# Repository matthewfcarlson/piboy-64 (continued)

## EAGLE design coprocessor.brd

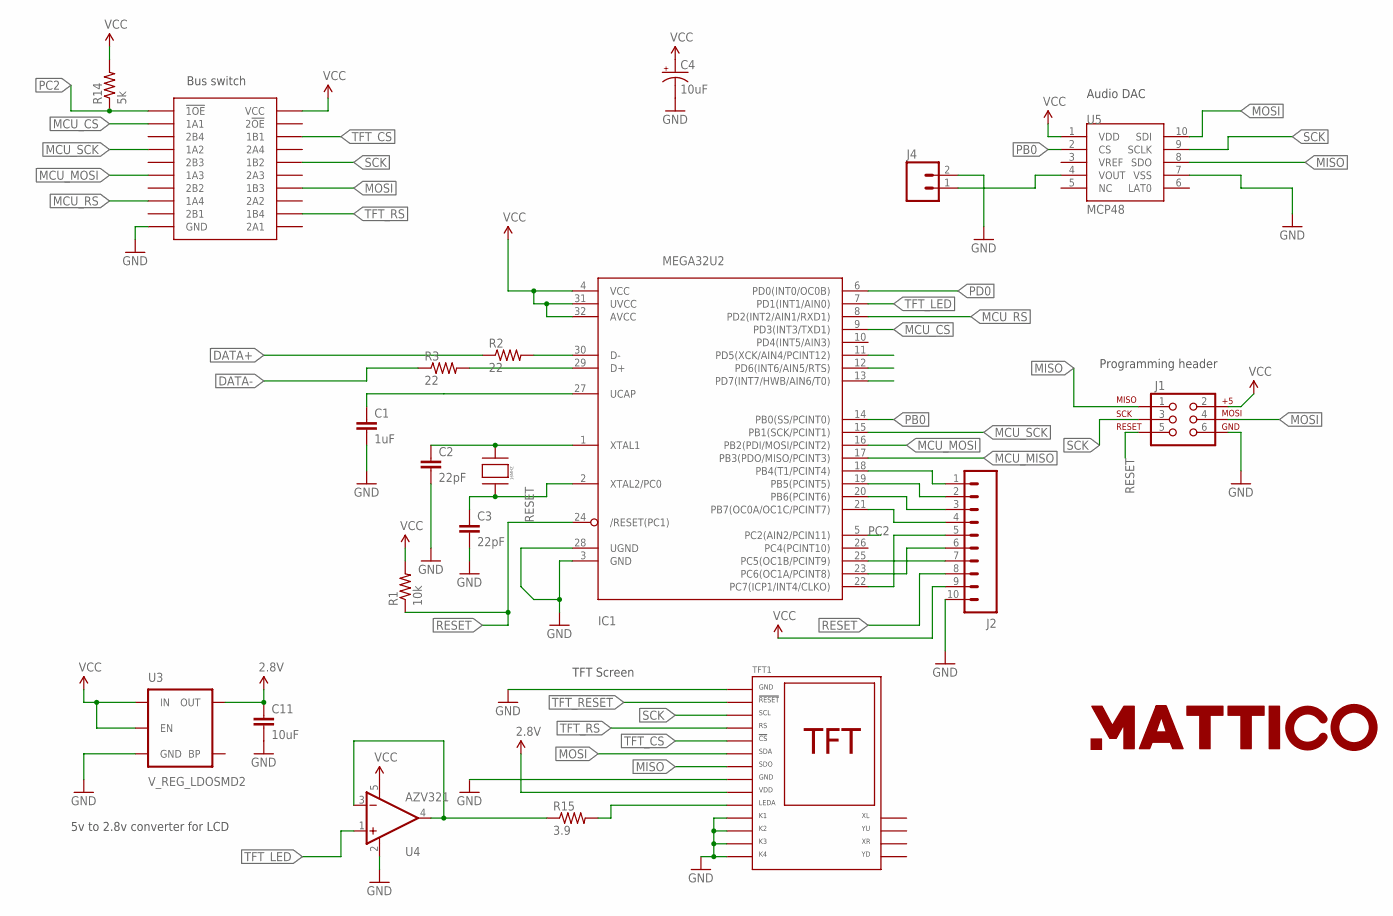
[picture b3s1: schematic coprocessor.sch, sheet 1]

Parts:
C1: 1uF; 0805
C2, C3: 22pF; 0805
C4: 10uF; EIA3216
C11: 10uF; 0805-CAP
IC1: MEGA32U2; TQFP32-08
J1: AVR_SPI_PRG_6NS; 2X3-NS
J2: M102MM; 1X10-2MM
J4: M02LOCK; 1X02_LOCK
R1: 10k; 0805
R2, R3: 22; 0805
R14: 5k; 0805
R15: 3.9; 0805
TFT1: TFT-18-1.0MM; TFT-CONN-18
U3: V_REG_LDOSMD2; SC70
U4: AZV321; SOT23-5
U5: MCP48; 10-MSOP
U6: 16MHZ; HC49/US
U7: CBT3244AD; S020-75MM
U$2: LOGO2INCH_SVG; LOGO_2INCH_SVG

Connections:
2.8V: C11.1, TFT1.9 (VDD), U3.5 (OUT)
DAC_VOUT: J4.1, U5.4 (VOUT)
DATA+: R2.1; also elsewhere on the board
DATA-: R3.1; also elsewhere on the board
GND: C1.2, C2.2, C3.2, C4.C (-), C11.2, IC1.3 (GND), IC1.28 (UGND), J1.6, J2.10, J4.2, TFT1.1 (GND), TFT1.8 (GND), TFT1.11 (K1), TFT1.12 (K2), TFT1.13 (K3), TFT1.14 (K4), U3.2 (GND), U4.2 (V-), U5.7 (VSS), U7.P$10 (GND); also elsewhere on the board
MCU_CS: IC1.9 (PD3(INT3/TXD1)), U7.P$2 (1A1)
MCU_MISO: IC1.17 (PB3(PDO/MISO/PCINT3))
MCU_MOSI: IC1.16 (PB2(PDI/MOSI/PCINT2)), U7.P$6 (1A3)
MCU_RS: IC1.8 (PD2(INT2/AIN1/RXD1)), U7.P$8 (1A4)
MCU_SCK: IC1.15 (PB1(SCK/PCINT1)), U7.P$4 (1A2)
MISO: J1.1, TFT1.7 (SDO), U5.8 (SDO)
MOSI: J1.4, TFT1.6 (SDA), U5.10 (SDI), U7.P$14 (1B3)
unnamed: IC1.29 (D+), R3.2
unnamed: IC1.30 (D-), R2.2
unnamed: IC1.18 (PB4(T1/PCINT4)), J2.1
unnamed: C1.1, IC1.27 (UCAP)
unnamed: C2.1, IC1.1 (XTAL1), U6.P$2
unnamed: C3.1, IC1.2 (XTAL2/PC0), U6.P$1
unnamed: R15.2, TFT1.10 (LEDA)
unnamed: R15.1, U4.3 (-IN), U4.4 (OUT)
unnamed: IC1.19 (PB5(PCINT5)), J2.2
unnamed: IC1.20 (PB6(PCINT6)), J2.3
unnamed: IC1.21 (PB7(OC0A/OC1C/PCINT7)), J2.4
unnamed: IC1.22 (PC7(ICP1/INT4/CLKO)), J2.5
unnamed: IC1.23 (PC6(OC1A/PCINT8)), J2.6
unnamed: IC1.25 (PC5(OC1B/PCINT9)), J2.7
PB0: IC1.14 (PB0(SS/PCINT0)), U5.2 (CS)
PC2: IC1.5 (PC2(AIN2/PCIN11)), R14.1, U7.P$1 (!1OE)
PD0: IC1.6 (PD0(INT0/OC0B))
PD5: IC1.11 (PD5(XCK/AIN4/PCINT12))
PD6: IC1.12 (PD6(INT6/AIN5/RTS))
PD7: IC1.13 (PD7(INT7/HWB/AIN6/T0))
RESET: IC1.24 (/RESET(PC1)), J1.5, J2.8, R1.1
SCK: J1.3, TFT1.3 (SCL), U5.9 (SCLK), U7.P$16 (1B2)
TFT_CS: TFT1.5 (!CS), U7.P$18 (1B1)
TFT_LED: IC1.7 (PD1(INT1/AIN0)), U4.1 (+IN)
TFT_RESET: TFT1.2 (!RESET)
TFT_RS: TFT1.4 (RS), U7.P$12 (1B4)
VCC: C4.A (+), IC1.4 (VCC), IC1.31 (UVCC), IC1.32 (AVCC), J1.2, J2.9, R1.2, R14.2, U3.1 (IN), U3.3 (EN), U4.5 (V+), U5.1 (VDD), U7.P$20 (VCC); also elsewhere on the board

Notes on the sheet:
Bus switch
5v to 2.8v converter for LCD
TFT Screen
Audio DAC
Programming header

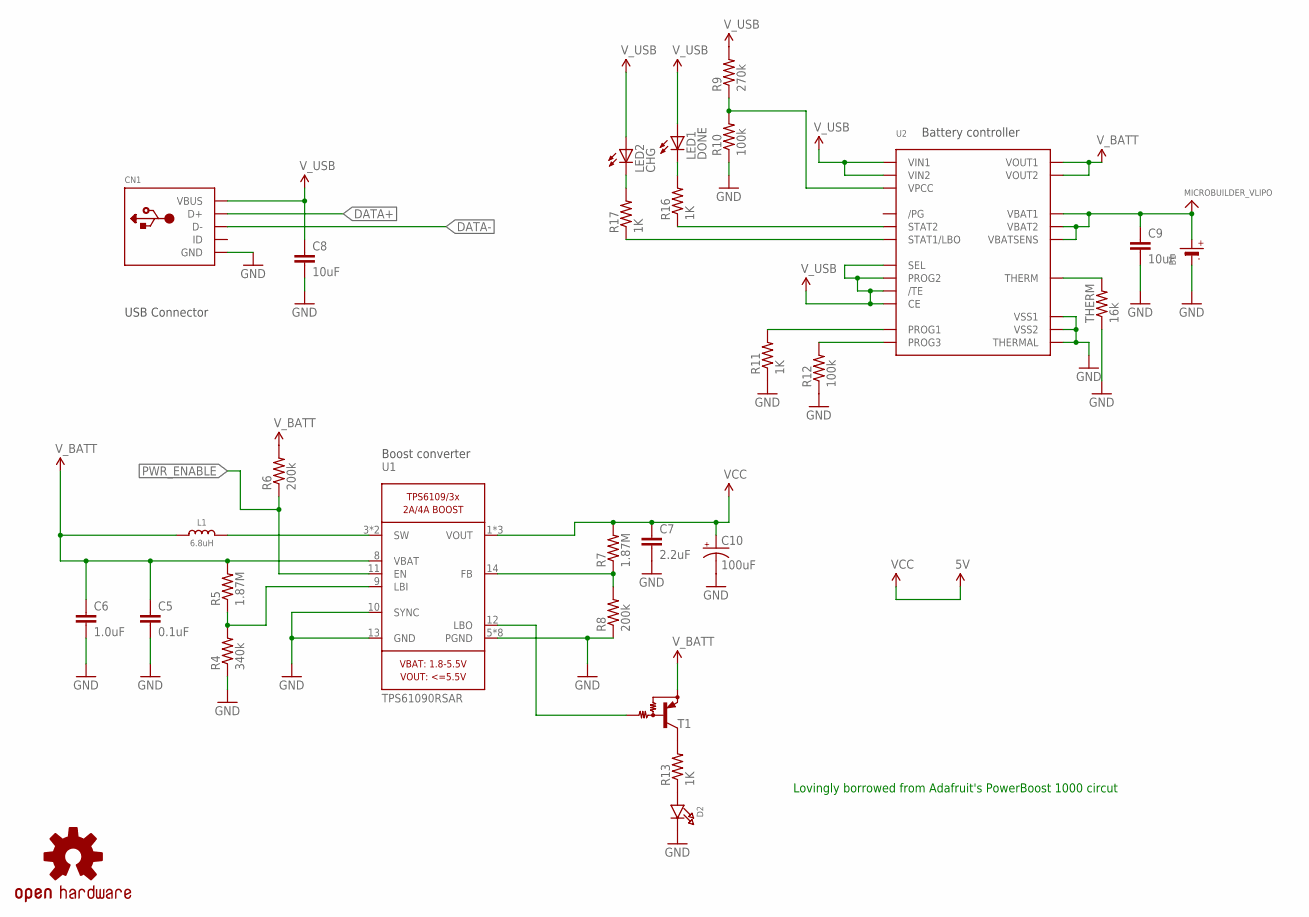
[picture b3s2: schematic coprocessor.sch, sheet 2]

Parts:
B1: MICROBUILDER_BATTERY; MICROBUILDER_JSTPH2
C5: 0.1uF; 0603-CAP
C6: 1.0uF; 0603-CAP
C7: 2.2uF; 0603-CAP
C8, C9: 10uF; 0603-CAP
C10: 100uF; EIA3216
CN1: USBMINIB; USB-MINIB
D2: MICROBUILDER_LED0603; MICROBUILDER_CHIPLED_0603
L1: 6.8uH; MICROBUILDER_INDUCTOR_4.9X4.9MM
LED1: DONE; CHIPLED_0603
LED2: CHG; CHIPLED_0603
LOGO1: OSHW-LOGOS; OSHW-LOGO-S
R4: 340k; 0603-RES
R5, R7: 1.87M; 0603-RES
R6, R8: 200k; 0603-RES
R9: 270k; 0603-RES
R10, R12: 100k; 0603-RES
R11, R13, R16, R17: 1K; 0603-RES
T1: TRANSISTOR_PNP_DRIVERMUN2111T1SC59-BEC; TRANSISTOR_SC59-BEC
THERM: 16k; 0603-RES
U1: TPS61090RSAR; MICROBUILDER_PVQFN-16
U2: MCP73871; MICROBUILDER_QFN20_4MM

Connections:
DATA+: CN1.D+; also elsewhere on the board
DATA-: CN1.D-; also elsewhere on the board
GND: B1.1 (-), C5.2, C6.2, C7.2, C8.2, C9.2, C10.C (-), CN1.GND, D2.C, R4.1, R8.1, R10.1, R11.1, R12.1, THERM.1, U1.5 (PGND), U1.6 (PGND), U1.7 (PGND), U1.10 (SYNC), U1.13 (GND), U1.P$18 (PGND), U1.P$19 (PGND), U1.P$20 (PGND), U1.P$21 (PGND), U1.P$22 (PGND), U2.P$10 (VSS1), U2.P$11 (VSS2), U2.P$21 (THERMAL); also elsewhere on the board
unnamed: R9.1, R10.2, U2.P$2 (VPCC)
unnamed: R4.2, R5.1, U1.9 (LBI)
unnamed: L1.P$2 (2), U1.3 (SW), U1.4 (SW)
unnamed: R11.2, U2.P$13 (PROG1)
unnamed: R7.1, R8.2, U1.14 (FB)
unnamed: R12.2, U2.P$12 (PROG3)
unnamed: T1.B, U1.12 (LBO)
unnamed: R13.2, T1.C
unnamed: D2.A, R13.1
unnamed: R16.1, U2.P$7 (STAT2)
unnamed: R17.1, U2.P$8 (STAT1/LBO)
unnamed: LED1.C, R16.2
unnamed: LED2.C, R17.2
unnamed: THERM.2, U2.P$5 (THERM)
PWR_ENABLE: R6.1, U1.11 (EN)
VCC: C7.1, C10.A (+), R7.2, U1.1 (VOUT), U1.15 (VOUT), U1.16 (VOUT); also elsewhere on the board
VLIPO: B1.2 (+), C9.1, U2.P$14 (VBAT1), U2.P$15 (VBAT2), U2.P$16 (VBATSENS)
V_BATT: C5.1, C6.1, L1.P$1 (1), R5.2, R6.2, T1.E, U1.8 (VBAT), U2.P$1 (VOUT1), U2.P$20 (VOUT2)
V_USB: C8.1, CN1.VBUS, LED1.A, LED2.A, R9.2, U2.P$3 (SEL), U2.P$4 (PROG2), U2.P$9 (/TE), U2.P$17 (CE), U2.P$18 (VIN1), U2.P$19 (VIN2)

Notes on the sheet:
USB Connector
Boost converter
Battery controller
Lovingly borrowed from Adafruit's PowerBoost 1000 circut

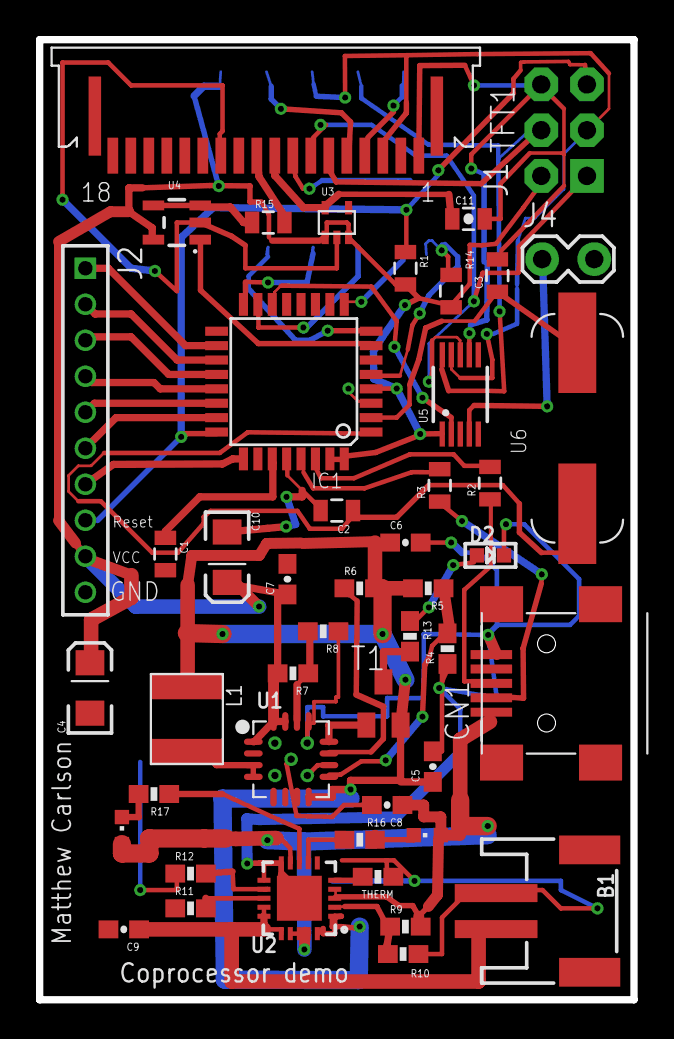
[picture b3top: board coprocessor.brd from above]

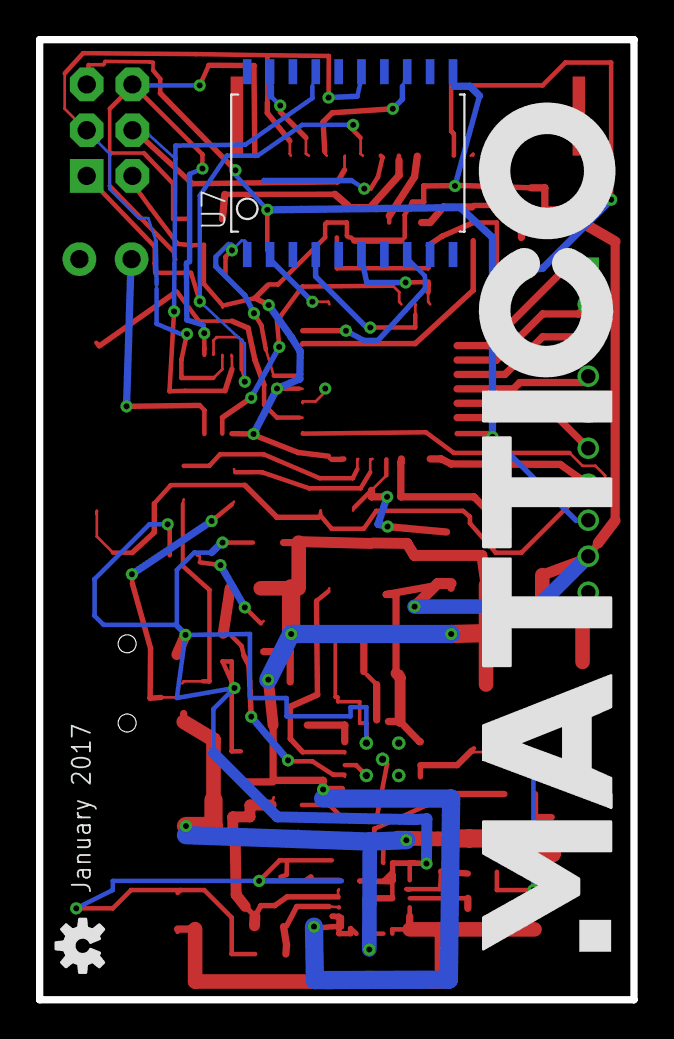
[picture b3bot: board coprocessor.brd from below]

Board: 2 copper layers, 33.0 x 53.3 mm, 50 parts (3 on the bottom side), 51 nets.

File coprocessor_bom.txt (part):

Partlist exported from C:/Users/matth/GitHub/piboy-64/coprocessor.sch at 4/5/2017 9:24 AM

Part  Value         Device                                 Package                           Description                                                                      PROD_ID    VALUE
B1                  MICROBUILDER_BATTERY                   MICROBUILDER_JSTPH2               CR1220 SMT - Digikey: 3001K-ND                                                                   
C1    1uF           CAP0805                                0805                              Capacitor                                                                                        
C2    22pF          CAP0805                                0805                              Capacitor                                                                                        
C3    22pF          CAP0805                                0805                              Capacitor                                                                                        
C4    10uF          CAP_POL1206                            EIA3216                           Capacitor Polarized                                                                              
C5    0.1uF         0.1UF-100V-10%(0603)                   0603-CAP                          CAP-08390                                                                        CAP-08390  0.1uF
C6    1.0uF         1.0UF-16V-10%(0603)                    0603-CAP                          CAP-00868                                                                        CAP-00868  1.0uF
C7    2.2uF         2.2UF-10V-20%(0603)                    0603-CAP                          CAP-07888                                                                        CAP-07888  2.2uF
C8    10uF          10UF-6.3V-20%(0603)                    0603-CAP                          CAP-11015                                                                        CAP-11015  10uF 
C9    10uF          10UF-6.3V-20%(0603)                    0603-CAP                          CAP-11015                                                                        CAP-11015  10uF 
C10   100uF         CAP_POL1206                            EIA3216                           Capacitor Polarized                                                                              
C11   10uF          10UF10V10%(0805)                       0805-CAP                          CAP-11330                                                                        CAP-11330       
CN1                 USBMINIB                               USB-MINIB                         USB Connectors                                                                                   
D2                  MICROBUILDER_LED0603                   MICROBUILDER_CHIPLED_0603         LED                                                                                              
IC1   MEGA32U2      ATMEGA32U2-TQFP                        TQFP32-08                         ATmega32u2                                                                                       
J1                  AVR_SPI_PRG_6NS                        2X3-NS                            AVR ISP 6 Pin                                                                                    
J2                  M102MM                                 1X10-2MM                          Header 10                                                                                        
J4                  M02LOCK                                1X02_LOCK                         Standard 2-pin 0.1" header. Use with                                                             
L1    6.8uH         MICROBUILDER_INDUCTORNR401             MICROBUILDER_INDUCTOR_4X4MM_NR401 Inductors                                                                                        
LED1  DONE          LEDCHIPLED_0603                        CHIPLED_0603                      LED                                                                                              
LED2  CHG           LEDCHIPLED_0603                        CHIPLED_0603                      LED                                                                                              
LOGO1 OSHW-LOGOS    OSHW-LOGOS                             OSHW-LOGO-S                       Open Source Hardware Logo                                                                        
R1    10k           RESISTOR0805-RES                       0805                              Resistor                                                                                         
R2    22            RESISTOR0805-RES                       0805                              Resistor                                                                                         
R3    22            RESISTOR0805-RES                       0805                              Resistor                                                                                         
R4    340k          340OHM-1/10W-1%(0603)                  0603-RES                          RES-12616                                                                        RES-12616  340  
R5    1.87M         1.8KOHM1/10W1%(0603)                   0603-RES                          RES-09119                                                                        RES-09119  1.8k 
R6    200k          200KOHM1/10W1%(0603)200K               0603-RES                          RES-09385                                                                        RES-09385  200k 
R7    1.87M         1.8KOHM1/10W1%(0603)                   0603-RES                          RES-09119                                                                        RES-09119  1.8k 
R8    200k          200KOHM1/10W1%(0603)200K               0603-RES                          RES-09385                                                                        RES-09385  200k 
R9    270k          220KOHM1/10W1%(0603)                   0603-RES                          RES-08969                                                                        RES-08969  220k 
R10   100k          100KOHM-1/10W-1%(0603)                 0603-RES                          RES-07828                                                                        RES-07828  100k 
R11   1K            1KOHM-1/10W-1%(0603)                   0603-RES                          RES-07856                                                                        RES-07856  1K   
R12   100k          100KOHM-1/10W-1%(0603)                 0603-RES                          RES-07828                                                                        RES-07828  100k 
R13   1K            1KOHM-1/10W-1%(0603)                   0603-RES                          RES-07856                                                                        RES-07856  1K   
R14   5k            RESISTOR0805-RES                       0805                              Resistor                                                                                         
R15   3.9           RESISTOR0805-RES                       0805                              Resistor                                                                                         
R16   1K            1KOHM-1/10W-1%(0603)                   0603-RES                          RES-07856                                                                        RES-07856  1K   
R17   1K            1KOHM-1/10W-1%(0603)                   0603-RES                          RES-07856                                                                        RES-07856  1K   
T1                  TRANSISTOR_PNP_DRIVERMUN2111T1SC59-BEC TRANSISTOR_SC59-BEC               PNP Bias Resistor Transistor                                                                     
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
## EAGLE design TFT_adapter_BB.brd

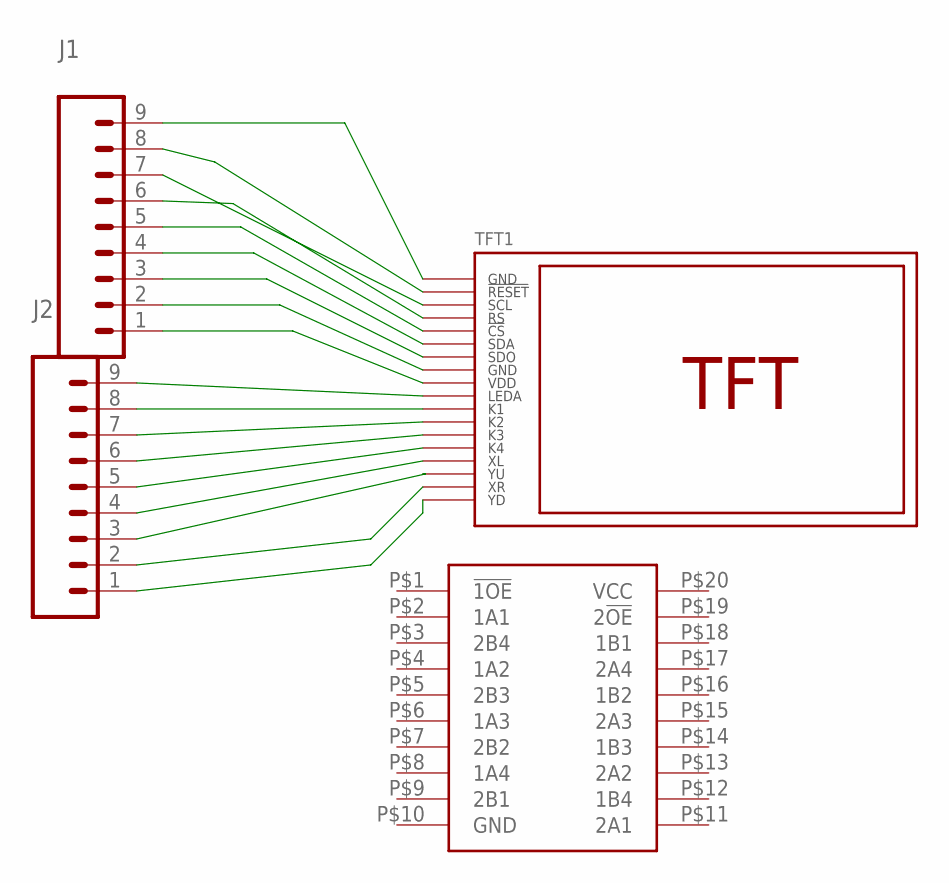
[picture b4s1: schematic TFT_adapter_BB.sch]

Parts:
J1, J2: M09NO_SILK; 1X09_NO_SILK
TFT1: TFT-18-1.0MM; TFT-CONN-18
U$1: CBT3244AD; S020-75MM

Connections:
GND: J1.3, J1.9, TFT1.1 (GND), TFT1.7 (SDO), U$1.P$10 (GND)
GND2: J1.2, TFT1.8 (GND)
LEDA: J2.9, TFT1.10 (LEDA)
unnamed: J1.8, TFT1.2 (!RESET)
unnamed: J1.7, TFT1.3 (SCL)
unnamed: J1.6, TFT1.4 (RS)
unnamed: J1.5, TFT1.5 (!CS)
unnamed: J1.4, TFT1.6 (SDA)
unnamed: J2.1, TFT1.18 (YD)
unnamed: J2.2, TFT1.17 (XR)
unnamed: J2.3, TFT1.16 (YU)
unnamed: J2.4, TFT1.15 (XL)
unnamed: J2.5, TFT1.14 (K4)
unnamed: J2.7, TFT1.12 (K2)
unnamed: J2.6, TFT1.13 (K3)
unnamed: J2.8, TFT1.11 (K1)
VCC: U$1.P$20 (VCC)
VDD: J1.1, TFT1.9 (VDD)

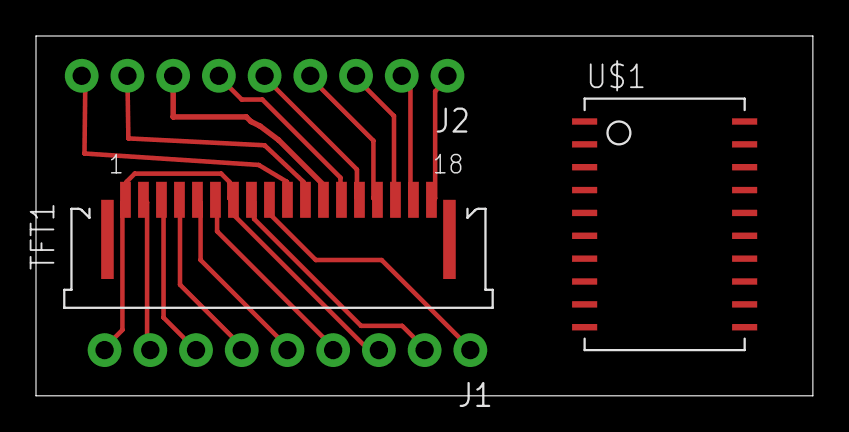
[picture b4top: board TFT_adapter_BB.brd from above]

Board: 2 copper layers, 43.2 x 20.0 mm, 4 parts (0 on the bottom side), 17 nets.

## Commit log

2016-11-09 updated git
2016-11-09 Removed the link socket and added micro USB
2016-11-10 added more connectors
2016-11-10 new board imae
2016-11-10 Added some resistors for the enable USB Boot
2016-11-10 Added connections for buttons
2016-11-11 I need to use a better uSD card layout
2016-11-16 added a smaller board for testing my SMD skills and prototyping the coprocessor
2016-11-17 added the co-processor and whatnot
2016-11-17 Changed the clearances to match 12 mils at shop
2016-11-19 redid the routing by hand
2016-11-21 new TFT adapter
2016-11-21 Added breadboard version of the TFT adapter
2016-11-22 Added the breadboard TFT adapater
2016-11-22 accidently deleted the coprocessor board
2016-12-12 Finished the coprocessor
2016-12-21 added the custom library and power controller
    started to integrate the custom power controller to the coprocessor
    board so it can be powered by the battery. I need to figure out how to
    enable the raspberry pi
2016-12-22 finished the power
2017-01-03 Added a few parts to the custom lib and added more to the coprocessor
2017-01-03 Updated the readme
2017-01-03 Added some renders of current progress
2017-01-05 Added a cool logo
2017-01-05 Added some aesthetics
2017-01-26 final schematic for revision 2
2017-01-26 fixed a minor bug on the Bus switch PB2->PC2
2017-03-01 addeda bill of materials
2017-03-24 finished routing the coprocessor board
2017-03-25 added the layouts
2017-03-27 updated the gerbers- fixed the pour and a few clearance issues.
2017-03-30 updated the crystal layout
2017-04-05 updates to the bus switch package and trace widths
2017-04-05 redid the inductor to save some space
    I noticed that I setup the charging circuit incorrectly
2017-04-07 had to just completely revamp the voltages
2017-04-07 added an SVG logo and redid the gerbers
2017-04-08 added new gerbers and ordered the board
2017-05-26 updates to the BOM
2017-05-27 lots of changes
    -startup sound
    -joystick
    -zbuttons
2017-05-27 added x&y buttons but they need work
2017-05-27 Added OSH park rules
2017-07-13 updated pdf render
2017-08-02 added co processor and usb hub chip
2017-08-03 added usb hub chip :)
2017-08-03 connected DAC directly to the Atmega
2017-08-03 moved some parts arounf
2017-08-04 added a uSD card slot and a few test points
2017-08-05 added the battery charging circuit
2017-08-05 added a fan for overheating?
2017-08-14 added the HDMI plug :/
2017-08-14 Added power generation sheet
2017-08-29 took out FTDI chip
2017-10-23 changed direction dramatically
    reduced the specs significantly. No HMDI out, no USB hub, no lipo
2017-10-31 removed joystick and a few other features :'-(
2017-10-31 Revert "removed joystick and a few other features :'-("
    This reverts commit c302e6474c1823b5cc4102c3b1e7e39d4d9bb988.
2017-10-31 removed joystick and file got corrupted
2017-10-31 added L2 and R2
2017-10-31 Added power regular
2017-10-31 added low battery comparer
2017-10-31 added low power LED
2017-10-31 added new parts and routed bus switch
2017-10-31 added more to the power circuit
2017-11-02 moved all buttons to pi instead of copro
2017-11-02 moved connectors and whatnot
2017-11-03 updated board render
2017-11-03 moved some labels around
2017-11-03 added power enable to Coprocessor
2017-11-03 added power down
2017-11-03 correctly wired power up and power down
2017-11-03 switch to proprocessor to 3.3v
2017-11-07 adding more power chips
2017-11-07 added a few grounding caps
2017-11-07 changed advanced schematic to Pi64 and added Ryan's version
2017-11-08 added coprocessor
2017-11-08 added AVR ISP
2017-11-08 switched to USB-mini :/
2017-11-08 added some descriptions and moved some labels
2017-11-12 almost done!
2017-11-14 added soureable switch
2017-11-14 added a sourceable switch
2017-11-14 still need to route power
2017-11-15 fixed erc
2017-11-15 last fixes
2017-11-15 added v1 gerbers
2017-11-22 added bill of materials
2018-10-25 Removed old stuff and started new circuit board design
2018-10-25 removed a lot of cruft and added STM32F
2018-10-25 Added PWR and GND to STM32
